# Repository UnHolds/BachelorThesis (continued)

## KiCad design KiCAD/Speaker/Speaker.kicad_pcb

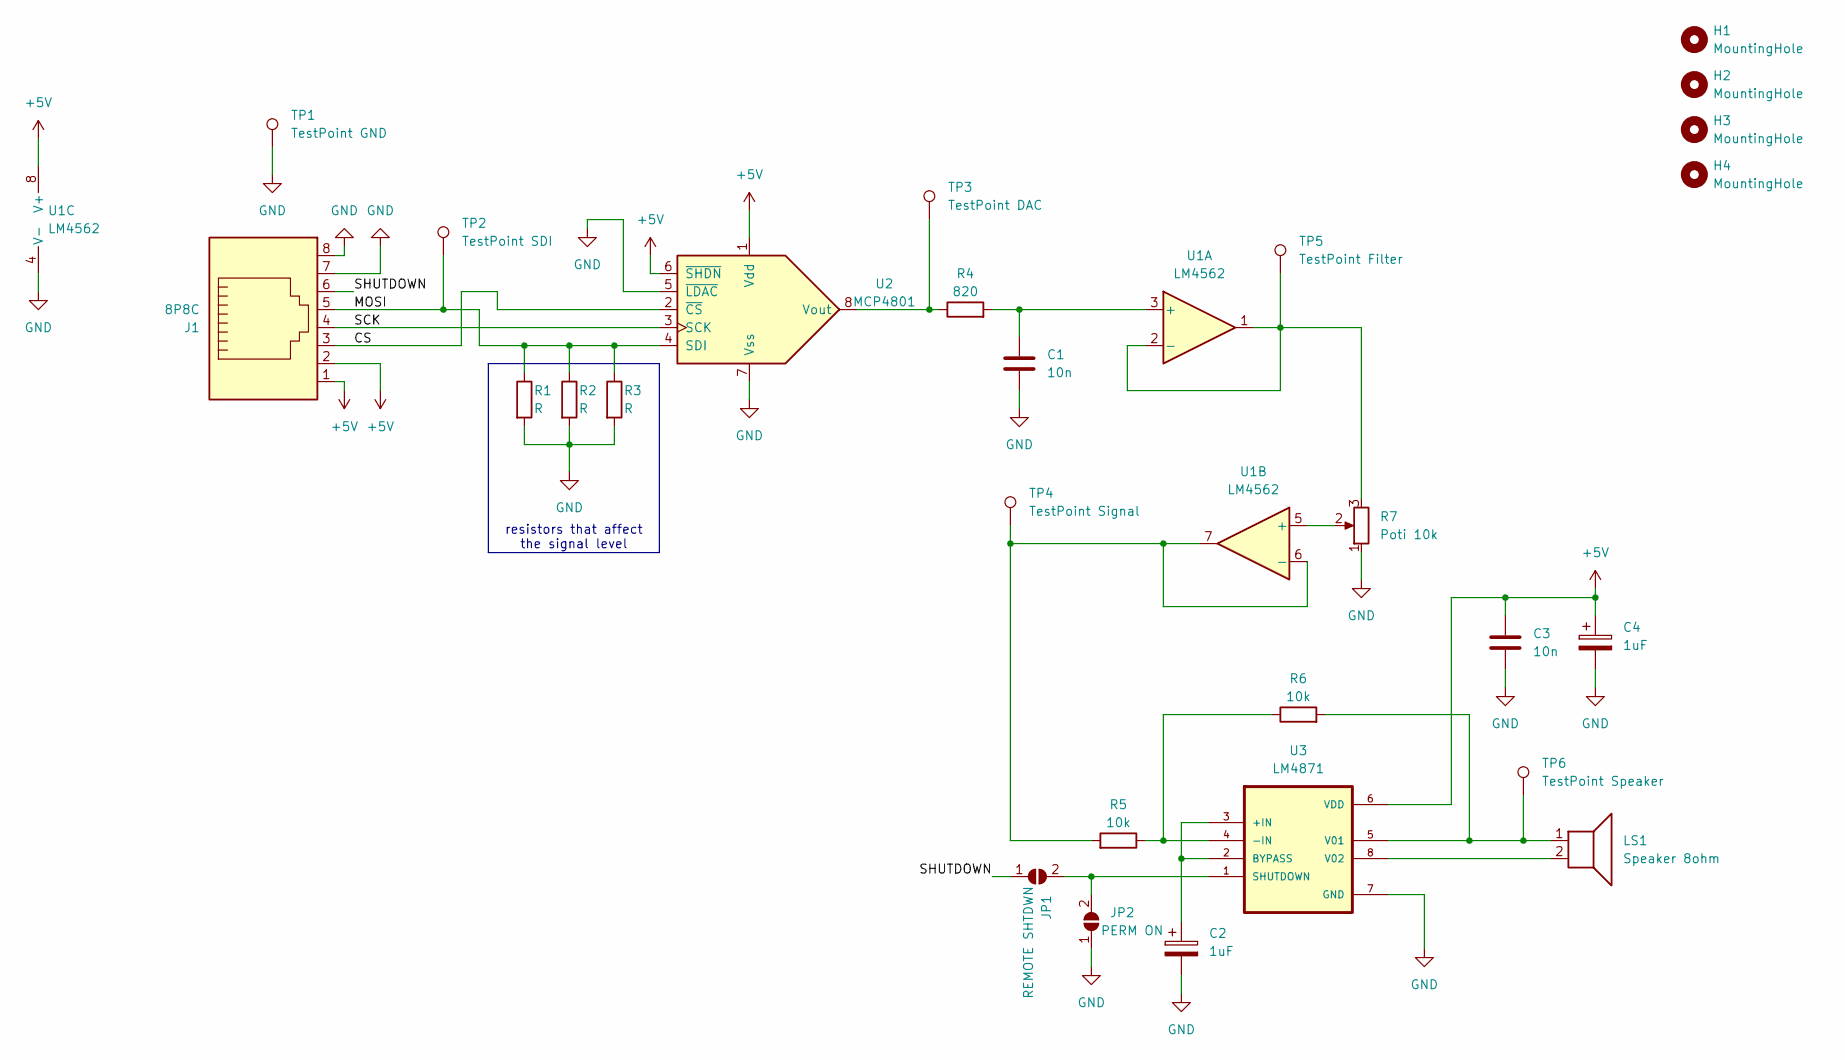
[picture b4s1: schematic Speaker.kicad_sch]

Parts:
C1, C3: 10n; C_1206_3216Metric_Pad1.33x1.80mm_HandSolder
C2, C4: 1uF; CP_Radial_D5.0mm_P2.50mm
H1, H2, H3, H4: MountingHole; MountingHole_3.2mm_M3
J1: 8P8C; RJ45_Amphenol_54602-x08_Horizontal_Custom
JP1: REMOTE SHTDWN; SolderJumper-2_P1.3mm_Open_Pad1.0x1.5mm
JP2: PERM ON; SolderJumper-2_P1.3mm_Open_Pad1.0x1.5mm
LS1: Speaker 8ohm; PinHeader_1x02_P2.54mm_Vertical
R1, R2, R3: R; R_0805_2012Metric_Pad1.20x1.40mm_HandSolder
R4: 820; R_0805_2012Metric_Pad1.20x1.40mm_HandSolder
R5, R6: 10k; R_0805_2012Metric_Pad1.20x1.40mm_HandSolder
R7: Poti 10k; Potentiometer_Piher_PT-6-V_Vertical
TP1: TestPoint GND; TestPoint_Loop_D2.54mm_Drill1.5mm_Beaded
TP2: TestPoint SDI; TestPoint_Loop_D2.54mm_Drill1.5mm_Beaded
TP3: TestPoint DAC; TestPoint_Loop_D2.54mm_Drill1.5mm_Beaded
TP4: TestPoint Signal; TestPoint_Loop_D2.54mm_Drill1.5mm_Beaded
TP5: TestPoint Filter; TestPoint_Loop_D2.54mm_Drill1.5mm_Beaded
TP6: TestPoint Speaker; TestPoint_Loop_D2.54mm_Drill1.5mm_Beaded
U1: LM4562; DIP-8_W7.62mm_Socket
U2: MCP4801; DIP-8_W7.62mm_Socket
U3: LM4871; SOIC-8_5.23x5.23mm_P1.27mm

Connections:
+5V: C3.1, C4.1, J1.1, J1.2, U1.8 (V+), U2.1 (Vdd), U2.6 (~SHDN), U3.6 (VDD)
/CS: J1.3, U2.2 (~CS)
/MOSI: J1.5, R1.1, R2.1, R3.1, TP2.1, U2.4 (SDI)
/SCK: J1.4, U2.3 (SCK)
/SHUTDOWN: J1.6, JP1.1 (A)
GND: C1.2, C2.2, C3.2, C4.2, J1.7, J1.8, J1.9, JP2.1 (A), R1.2, R2.2, R3.2, R7.1, TP1.1, U1.4 (V-), U2.5 (~LDAC), U2.7 (Vss), U3.7 (GND)
unnamed: JP1.2 (B), JP2.2 (B), U3.1 (SHUTDOWN)
unnamed: C1.1, R4.2, U1.3 (+)
unnamed: R7.3, TP5.1, U1.1, U1.2 (-)
unnamed: R7.2, U1.5 (+)
unnamed: R5.2, TP4.1, U1.6 (-), U1.7
unnamed: R4.1, TP3.1, U2.8 (Vout)
unnamed: C2.1, U3.2 (BYPASS), U3.3 (+IN)
unnamed: R5.1, R6.1, U3.4 (-IN)
unnamed: LS1.1, R6.2, TP6.1, U3.5 (V01)
unnamed: LS1.2, U3.8 (V02)

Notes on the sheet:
resistors that affect the signal level

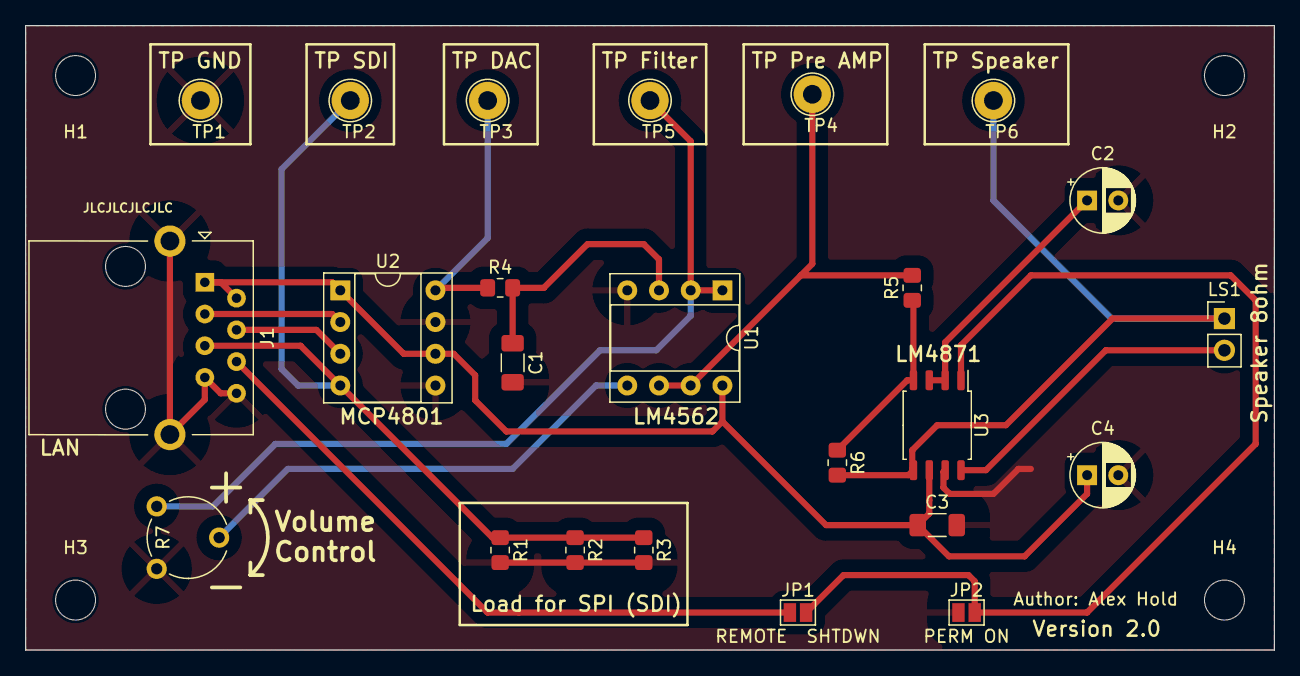
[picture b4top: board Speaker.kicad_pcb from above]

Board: 2 copper layers, 100.0 x 50.0 mm, 28 parts (0 on the bottom side), 16 nets.

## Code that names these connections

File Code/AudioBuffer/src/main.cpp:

#include <Arduino.h>
#include "FS.h"
#include "SD.h"
#include "SPI.h"
#include "ESP32DMASPISlave.h"
#include <FastLED.h>
#include <vector>

#define CS_PIN_SD_CARD 5
#define BUFFER_SIZE 4096
#define N_QUEUES 4

//Buttons
#define MISC_BUTTON 35
#define NEXT_SONG_BUTTON 34
#define PLAY_PAUSE_BUTTON 4
#define PREVIOUS_SONG_BUTTON 21

#define COM_C1 32
#define COM_C2 25
#define COM_C3 26
#define COM_C4 27

#define WS2812_PIN 22

/*
##### MODE ######
0 = OFF
1 = Single ALL
2 = 5 Different
*/

#define NUM_LEDS 8
CRGB leds[NUM_LEDS];
bool led_change = false;
File audio_file;
ESP32DMASPI::Slave slave;

uint8_t *audio_buffer[N_QUEUES];
uint8_t *rx_buffer;
int next_buffer = 0;

int mode = 0;
bool mode_change = true;
std::vector<String> songs;
int num_songs = 0;
int current_song = 0;
bool play = false;

void fill_buffer(int queue_id)
{
    if (audio_file.available() <= 0)
    {
        audio_file.seek(0);
    }

    for(int i = 0; i < 8; i++){
        audio_buffer[queue_id][i] = 0;
    }

    int available_data = audio_file.available();
    int bytes_to_read = BUFFER_SIZE - 8;

    //handle pause
    if(play == false){
        for(int i = 0; i < bytes_to_read; i++){
            audio_buffer[queue_id][i + 8] = 0;
        }
        return;
    }


    int remaining_data = 0;
    if (available_data < BUFFER_SIZE - 8)
    {
        bytes_to_read = available_data;
        remaining_data = BUFFER_SIZE - 8 - available_data;
    }

    audio_file.read(audio_buffer[queue_id] + 8, bytes_to_read);

    if (remaining_data > 0)
    {
        audio_file.seek(0);
        audio_file.read(audio_buffer[queue_id] + bytes_to_read + 8, remaining_data);
    }
}

void setAudioFile(String filename){
    File tmp_audio_file = SD.open(filename, FILE_READ);

    if (!tmp_audio_file)
    {
        return;
    }

    tmp_audio_file.seek(0);
    audio_file = tmp_audio_file;
}

void setup_buffers()
{
    rx_buffer = slave.allocDMABuffer(BUFFER_SIZE);

    // create and fill buffer
    for (int i = 0; i < N_QUEUES; i++)
    {
        audio_buffer[i] = slave.allocDMABuffer(BUFFER_SIZE);
        fill_buffer(i);

    }

    // setup spi
    slave.setDataMode(SPI_MODE0);
    slave.setMaxTransferSize(BUFFER_SIZE);
    slave.setQueueSize(N_QUEUES);
    slave.begin(HSPI);

    for(int i = 0; i < N_QUEUES; i++){
       slave.queue(rx_buffer, audio_buffer[i], BUFFER_SIZE);
    }
}

void set_leds_black(){
    for(int i = 0; i < NUM_LEDS; i++){
        leds[i] = CRGB(0,0,0);
    }
}

void setup_sd_card()
{
    if (!SD.begin(CS_PIN_SD_CARD, SPI, 2000000))
    {
        return;
    }
    uint8_t cardType = SD.cardType();

    if (cardType == CARD_NONE)
    {
        return;
    }

    File root = SD.open("/");
    File file = root.openNextFile();
    num_songs = 0;
    while(file){
        String name = file.name();
        if(file.isDirectory() == false && name.endsWith(".bwav")){
            songs.push_back(file.path());
            num_songs++;
        }
        file.close();
        file = root.openNextFile();
    }
    root.close();

    setAudioFile(songs[current_song]);

    set_leds_black();
    leds[0] = CRGB(0,0,128);
    led_change = true;
    mode = songs[current_song][4] - 48;
    mode_change = true;
}



void setup()
{
    //Buttons
    pinMode(MISC_BUTTON, INPUT);
    pinMode(NEXT_SONG_BUTTON, INPUT);
    pinMode(PLAY_PAUSE_BUTTON, INPUT);
    pinMode(PREVIOUS_SONG_BUTTON, INPUT);

    pinMode(COM_C1, OUTPUT);
    pinMode(COM_C2, OUTPUT);
    pinMode(COM_C3, OUTPUT);
    pinMode(COM_C4, OUTPUT);

    FastLED.addLeds<WS2812B, WS2812_PIN, RGB>(leds, 4);

    //Serial.begin(115200);
    pinMode(LED_BUILTIN, OUTPUT);
    digitalWrite(LED_BUILTIN, LOW);
    setup_sd_card();
    setup_buffers();
    delay(1000);
}

bool butten_pressed = false;

void handleButtons() {

    int misc_press = digitalRead(MISC_BUTTON);
    int next_press = digitalRead(NEXT_SONG_BUTTON);
    int play_pause_press = digitalRead(PLAY_PAUSE_BUTTON);
    int previous_press = digitalRead(PREVIOUS_SONG_BUTTON);

    if(!misc_press && !next_press && !play_pause_press && !previous_press){
        butten_pressed = false;
    }

    //handle double press
    if(butten_pressed){
        return;
    }

    if(previous_press || next_press) {
        current_song = (current_song + num_songs - 1 * previous_press + 1 * next_press) % num_songs;
        setAudioFile(songs[current_song]);
        led_change = true;
        mode = songs[current_song][4] - 48;
        mode_change = true;
        set_leds_black();
        leds[current_song % NUM_LEDS] = CRGB(0,0,128);
        butten_pressed = true;
    }

    if(play_pause_press){
        play = !play;
        leds[current_song % NUM_LEDS] = CRGB(0,0,128);
        led_change = true;
        butten_pressed = true;
    }

    if(misc_press){
        butten_pressed = true;
        //todo do something
    }
}

void handleLeds(){
    if(led_change){
        FastLED.show();
        led_change = false;
    }
}

void set_mode() {
    if(mode_change){
        mode_change = false;
        digitalWrite(COM_C1, (mode & 0b1) > 0);
        digitalWrite(COM_C2, (mode & 0b10) > 0);
        digitalWrite(COM_C3, (mode & 0b100) > 0);
        digitalWrite(COM_C4, (mode & 0b1000) > 0);
    }
}

bool blink_led_on = true;
void blink(){
    if(blink_led_on){
        leds[current_song % NUM_LEDS] = CRGB(0,0,0);
    }else{
        leds[current_song % NUM_LEDS] = CRGB(0,0,128);
    }
    blink_led_on = !blink_led_on;
    led_change = true;
}

long last_millis = millis();

void loop()
{

    if(slave.available() > 0){
        slave.pop();
    }

    handleButtons();
    set_mode();
    handleLeds();
    if(last_millis + 750 < millis() && play == false){
        blink();
        last_millis = millis();
    }


    if(slave.remained() >= N_QUEUES){
        return;
    }

    fill_buffer(next_buffer);
    slave.queue(rx_buffer, audio_buffer[next_buffer], BUFFER_SIZE);
    delay(10);

    //fill up the next buffer
    next_buffer++;
    next_buffer %= N_QUEUES;
}

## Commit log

2022-12-12 init
2022-12-12 added .gitignore
2022-12-12 added initial note
2023-01-05 updated documentation
2023-01-08 added more infos to the possible topics + created note for the mail to the prof
2023-02-02 added bill of material to the docs
2023-02-18 added spice model for 8bit dac
2023-02-20 updatede simulation
2023-02-20 changed dac so that custom number of states can be used
2023-02-20 added calculations for the filter
2023-02-20 added model asy and added more doc on the calculations + doc for model code + schematic
2023-02-21 updated invert for images
2023-02-22 added simulation for metastable nand gatter
2023-02-25 added 74HCXX gates
2023-02-25 added ltspice gitignore
2023-02-25 added simulation for metastable nands
2023-02-25 added simulation text + pictures
2023-02-25 updated gitignore
2023-02-25 added simulation data
2023-02-25 added tool to print ltspice plots
2023-02-25 added x and y labels to plot
2023-02-25 added transient plot
2023-02-27 added missing simulation plots
2023-02-27 fixed spelling and linking
2023-02-27 now ltspice plotter supports multi y axis
2023-02-27 added transient simulation for normal operation
2023-02-27 added maximum ratings simulation and moved pictures
2023-02-27 fixed second axis detection
2023-02-27 updated tool now transparent by default
2023-02-27 added simulation of the lowpass filter
2023-02-28 added FFT simulation for I2C speaker
2023-02-28 added ignore for .fft files
2023-02-28 updated schematic svg
2023-03-01 added invert white
2023-03-01 moved files
2023-03-05 Added experiment explaination
2023-03-05 fixed some linking
2023-03-05 added code for nand gatter experiment
2023-03-07 added setup code for spi transfer
2023-03-07 added code for second dac
2023-07-22 added code for the first experiment
2023-07-22 added papers will be cited in the thesis
2023-07-24 completed experiment code
2023-07-25 added experiment data
2023-07-25 Added matplot to plot experiment data
2023-07-25 added git ignore for kicad
2023-07-25 added kicad files for experiment
2023-07-25 updated kicad
2023-07-25 moved experiment
2023-07-25 added 3.3V experiment data
2023-07-31 add 3_3 C data
2023-07-31 added 5V with cap data
2023-08-06 added code for next experiment
2023-08-06 fixed format
2023-08-06 added python tool that can generate wave forms
2023-08-23 fixed signal generator signal
2023-08-23 fixed code
2023-08-25 added simulation info
2023-09-03 added audio test support
2023-09-03 updated time stamps
2023-09-04 added custom binary wav builder
2023-09-04 changed song
2023-09-04 added speaker code that reads the information from an SD card
2023-09-04 added steckerbelegung rj45
2023-09-09 added PCB for speaker
2023-09-09 changed vspi to hspi for audio
2023-09-13 added new code for esp32 as buffer
2023-09-13 added first version plots
2023-09-13 added 3d models
2023-09-13 added drawings
2023-09-15 added PCB step file
2023-09-15 added audio via DMA
2023-09-15 added logic for DMA driven audio
2023-09-15 added another sample audio
2023-09-15 updated kicad files
2023-09-15 added print for sample rate
2023-09-15 bigger buffers
2023-09-19 reduced frequency and added led while loading
2023-09-19 added markdown for the ampelschaltung
2023-09-19 added dxf files
2023-09-19 remove backup files
2023-09-19 added gitignore freecad
2023-10-12 added spectrums of speaker
2023-10-24 changed schemtatic to version 2.1
2023-10-24 fixed DMA SPI transfer
2023-10-24 added viewer for bwav files
2023-10-24 added binary file creation for signalArrayCreator
2023-10-24 created PCB for version 2
2023-10-24 fixed top housing component
2023-11-26 added plots + new audio controller
2023-11-28 added pictures
2023-11-28 added experiment images to obsidian
2023-11-28 added i2c lautsprecher experiment images
2023-11-28 added label to plotter
2023-11-29 added paper for cap selection
2023-11-29 added buttons and leds to audio controller
2023-12-01 added audio controller pcb
2023-12-01 added BNC connector model
2023-12-01 updated prototyp page
2023-12-01 removed lock file
2023-12-06 added code for the next experiment
2023-12-07 added nand experiment 2
2023-12-08 fixed pin assignment sd-card
2023-12-08 added termine
2023-12-09 fixed pin assignments
2023-12-09 added button read
2023-12-09 added new music files
2023-12-09 added audio switching to buffer
2023-12-09 changed CS selector
2023-12-09 added merged play style
2023-12-09 added binary wave merger
2023-12-10 added new images if nand
2023-12-10 added code to control the dac via serial
2023-12-10 added text for the experiments (pictures missing)
2023-12-10 fixed code for plotter
2023-12-10 added experiment images
2023-12-10 added images for automated measurements
2023-12-10 added images + information about audio controller prototyp v1
2023-12-13 updated termine
2023-12-19 added support for 5 concurrent audio stream
2023-12-19 added multi wav merger
2023-12-19 renamed doc file + added new audio
2023-12-19 added simple ampelschaltung
2023-12-20 added adapter schematic
2023-12-20 added images + some more text
2023-12-20 added new termine
2024-01-07 added cable adapter pcb
2024-01-07 added mounting holes
2024-01-15 added schematic ampelschaltung
2024-01-17 update obsidian
2024-01-17 update pcb
2024-01-17 added image refs
2024-01-18 added ampelschaltung PCB
2024-01-18 added images
2024-01-28 routed ampelschaltung
2024-01-31 added ws2812 support
2024-01-31 updated schematic
2024-01-31 routed audio controller + added jlc string
2024-02-05 added new plots
2024-02-29 changed code for controller v2
2024-03-02 added housing for controller + adapter + ampel
2024-03-04 added export and fixed dimensions
2024-03-04 Added images for newly produced PCBs + added 3D models
2024-03-05 termine update
2024-03-06 added slides that will be used in the prolog
2024-03-06 some cleanup + updated gitignore + add obsidian page
2024-03-06 added plotdata
2024-03-06 moved slides add submodule
2024-03-06 removed old slides
2024-03-06 updated slides
2024-03-07 bump module
2024-03-12 Added preslides
2024-03-12 bump version
2024-03-12 bump
2024-03-12 added slide update info + neue termine
2024-03-15 updated slides + added resistor calc tool
2024-03-15 check folien checkboxes
2024-03-25 bump slides
2024-04-14 added new images / modified images for the BA
2024-04-18 meeting update
2024-04-20 added schematics
2024-04-20 added png of schematics
2024-04-20 updated housing
2024-04-21 updated code + added new functionality
2024-04-21 updated binary wave merger
2024-04-25 removed folder + added latex folder
2024-04-25 added readme + remove unused script
2024-04-29 added invoices
2024-05-01 fixed audio selection code + added new song
2024-05-01 updated readme for tools
2024-05-03 added new bwav files
